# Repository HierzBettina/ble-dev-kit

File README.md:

*Note*: I have ceased working on projects with the HM-10 and the CC2541. The difficulties of dealing with the IAR toolchain are too great. I now recommend [ARM mbed solutions](https://developer.mbed.org/platforms/Nordic-nRF51822/) if you intend to pursue developing a BLE peripheral. I am leaving the resources I was able to gather online in case someone has use for them, but I cannot provide support.

BLE Dev Kit
====

Getting into low power Bluetooth peripheral prototyping can get expensive quickly. This project aims to chart out and the document the cheapest, easiest way to create a true, custom peripheral with its own profile. Head on over the [wiki](https://github.com/nickswalker/ble-dev-kit/wiki) to read more.

Hardware
----
A sub ten dollar CC2541 development board based on the HM-10 module. This board is a fork of Ladvien's excellent work with the module.
 
Firmware
----
On-board application and profile examples.

Software
----
Client application examples (iOS).

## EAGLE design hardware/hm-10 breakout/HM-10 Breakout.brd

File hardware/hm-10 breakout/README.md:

HM-10 Breakout Board
====================

This is a slight modification of [Ladvien's board](https://github.com/Ladvien/HM-10). This version has more accurate pin notations and removes routes to unused pins on the HM-10, thereby shrinking the overall footprint of the board. 
The HM-10's on board TI CC2541 is fully programmable with CC-Debugger or SmartRF04EB. See this repo's [wiki](https://github.com/nickswalker/HM-10-breakout-board/wiki) for more resources.

## Bill of Materials

If you are planning on ordering the PCB through OSHPark, keep in mind that you will receive three copies. You may want to go ahead and order three times as many components. Digi-Key numbers are provided as a courtesy; check eBay or any other preferred supplier for better pricing. As long as the component matches the packaging a specifications, it should be fine.

At a bare minimum, the PCB and the HM-10 module are required. If you want to use UART but only have the capability of providing 5v, you will want to populate the level conversion components. However, this is /grossly/ inefficient and defeats the purpose of using a low power connection technology. Bridge the solder jumper to bypass the regulator circuit. You may consider simply regulating off board for development, using a cheap level converter like [this one](http://www.ebay.com/itm/1PC-New-5V-3V-IIC-UART-Level-Converter-Module-Adapter-4-Way-For-Arduino-/251384699933?pt=LH_DefaultDomain_0&hash=item3a87b21c1d).

Part (Digi-Key #) | Quantity | Optional (Required For)
:---------------- | :-------:| :----------------------
[Breakout PCB](https://oshpark.com/shared_projects/A6hoH6Fi)  | 1 | No
[HM-10 Module](http://www.fasttech.com/products/0/10004051/1292002-ti-cc2540-bluetooth-40-ble-2540-transparent-serial) | 1 | No
[0805 20kΩ Resistor](http://www.digikey.com/product-detail/en/RMCF0805JT20K0/RMCF0805JT20K0CT-ND/1942580) (RMCF0805JT20K0CT-ND) | 1 | Yes (UART level conversion)
[0805 10kΩ Resistor](http://www.digikey.com/product-detail/en/RMCF0805FT10K0/RMCF0805FT10K0DKR-ND/1943341) (RMCF0805FT10K0CT-ND) | 3 | Yes (UART level conversion)
[0603 LED](http://www.digikey.com/product-detail/en/LTST-C191KRKT/160-1447-1-ND/386836) (160-1447-1-ND) | 1 | Yes (LEDs)
[0603 LED (>3v drop)](http://www.digikey.com/product-detail/en/APT1608QBC%2FD/754-1434-1-ND/2163792) (754-1434-1-ND) | 2 | Yes (LEDs)
[0805 470Ω Resistor](http://www.digikey.com/product-detail/en/RMCF0805JG470R/RMCF0805JG470RCT-ND/4425246) (RMCF0805JG470RCT-ND) | 3 | Yes (LEDs)
[SOT-23 MCP1700 Voltage Regulator](http://www.digikey.com/product-detail/en/MCP1700T-3302E%2FTT/MCP1700T3302ETTCT-ND/652677) (MCP1700T3302ETTCT-ND) | 1 | Yes (voltage regulator)
[0805 1uF Capacitor](http://www.digikey.com/product-detail/en/JMK105BJ105KV-F/587-1231-1-ND/931008) (587-1231-1-ND) | 1 | Yes (Voltage regulator)

The silkscreen doesn't include values, so be sure to have it open in front of you while you assemble.

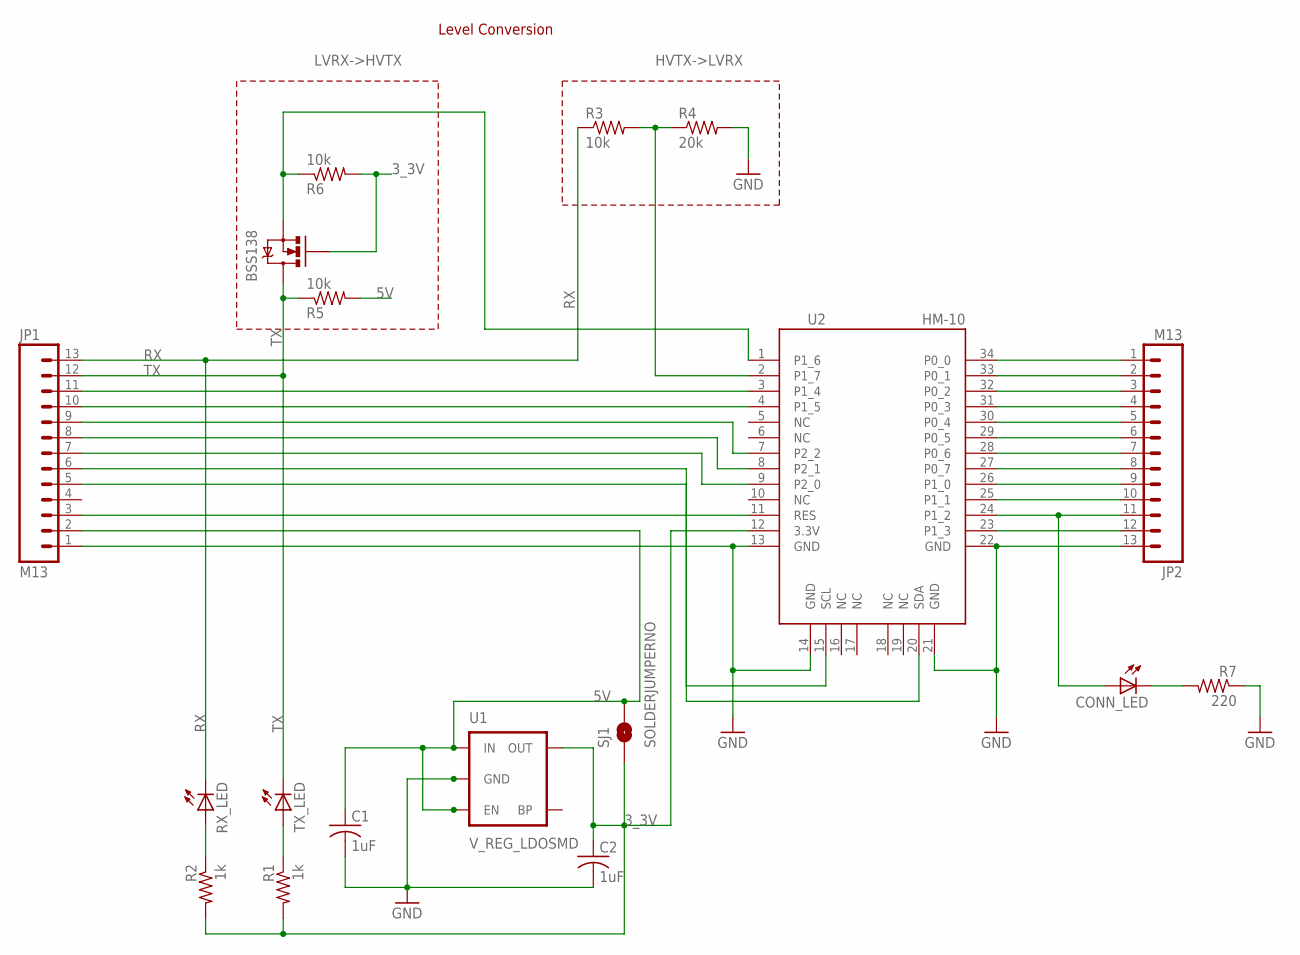
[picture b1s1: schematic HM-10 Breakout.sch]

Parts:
BSS138: MOSFET-NCHANNELSMD; SOT23-3
C1, C2: 1uF; C0805K
CONN_LED: LED0603; LED-0603
JP1, JP2: M13; 1X13
R1, R2: 1k; M0805
R3, R5, R6: 10k; M0805
R4: 20k; M0805
R7: 220; M0805
RX_LED: LED0603; LED-0603
SJ1: SOLDERJUMPERNO; SJ_2S-NO
TX_LED: LED0603; LED-0603
U1: V_REG_LDOSMD; SOT23-5
U2: HM-10

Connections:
3_3V: BSS138.1 (G), C2.1, R1.2, R2.2, R6.2, SJ1.1, U1.5 (OUT), U2.12 (3.3V)
5V: C1.1, JP1.2, R5.2, SJ1.2, U1.1 (IN), U1.3 (EN)
GND: C1.2, C2.2, JP1.1, JP2.13, R4.2, R7.1, U1.2 (GND), U2.13 (GND), U2.14 (GND), U2.21 (GND), U2.22 (GND)
HVTX->LVRX: R3.2, R4.1, U2.2 (P1_7)
LVRX->HVTX: BSS138.2 (S), R6.1, U2.1 (P1_6)
unnamed: CONN_LED.A, JP2.11, U2.24 (P1_2)
unnamed: JP1.3, U2.11 (RES)
unnamed: JP1.5, U2.15 (SCL)
unnamed: JP1.9, U2.7 (P2_2)
unnamed: JP1.8, U2.8 (P2_1)
unnamed: JP1.7, U2.9 (P2_0)
unnamed: JP2.10, U2.25 (P1_1)
unnamed: JP1.6, U2.20 (SDA)
unnamed: JP1.10, U2.4 (P1_5)
unnamed: JP1.11, U2.3 (P1_4)
unnamed: JP2.9, U2.26 (P1_0)
unnamed: JP2.8, U2.27 (P0_7)
unnamed: JP2.7, U2.28 (P0_6)
unnamed: JP2.6, U2.29 (P0_5)
unnamed: JP2.5, U2.30 (P0_4)
unnamed: JP2.4, U2.31 (P0_3)
unnamed: JP2.3, U2.32 (P0_2)
unnamed: JP2.2, U2.33 (P0_1)
unnamed: JP2.1, U2.34 (P0_0)
unnamed: JP2.12, U2.23 (P1_3)
unnamed: R1.1, TX_LED.A
unnamed: CONN_LED.C, R7.2
unnamed: R2.1, RX_LED.A
RX: JP1.13, R3.1, RX_LED.C
TX: BSS138.3 (D), JP1.12, R5.1, TX_LED.C

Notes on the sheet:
Level Conversion

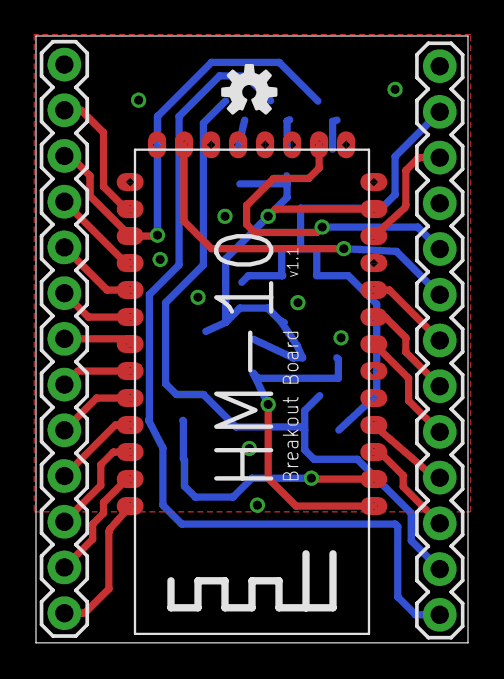
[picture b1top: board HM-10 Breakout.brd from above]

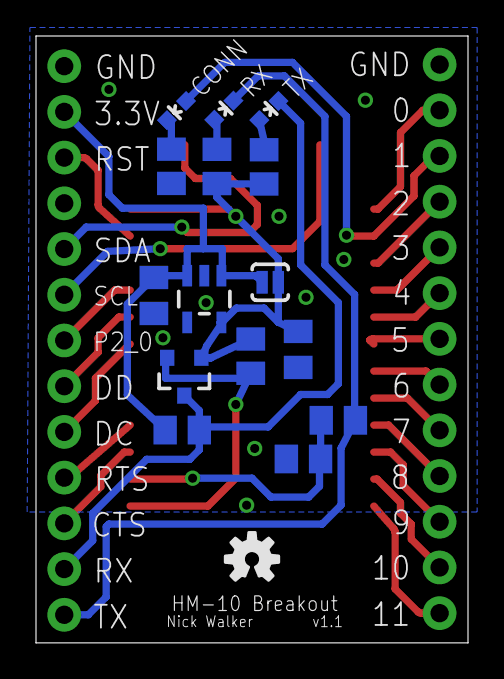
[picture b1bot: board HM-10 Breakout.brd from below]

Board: 2 copper layers, 24.0 x 33.7 mm, 20 parts (16 on the bottom side), 30 nets.

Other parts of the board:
U$1, U$2: OSHW-LOGO-S

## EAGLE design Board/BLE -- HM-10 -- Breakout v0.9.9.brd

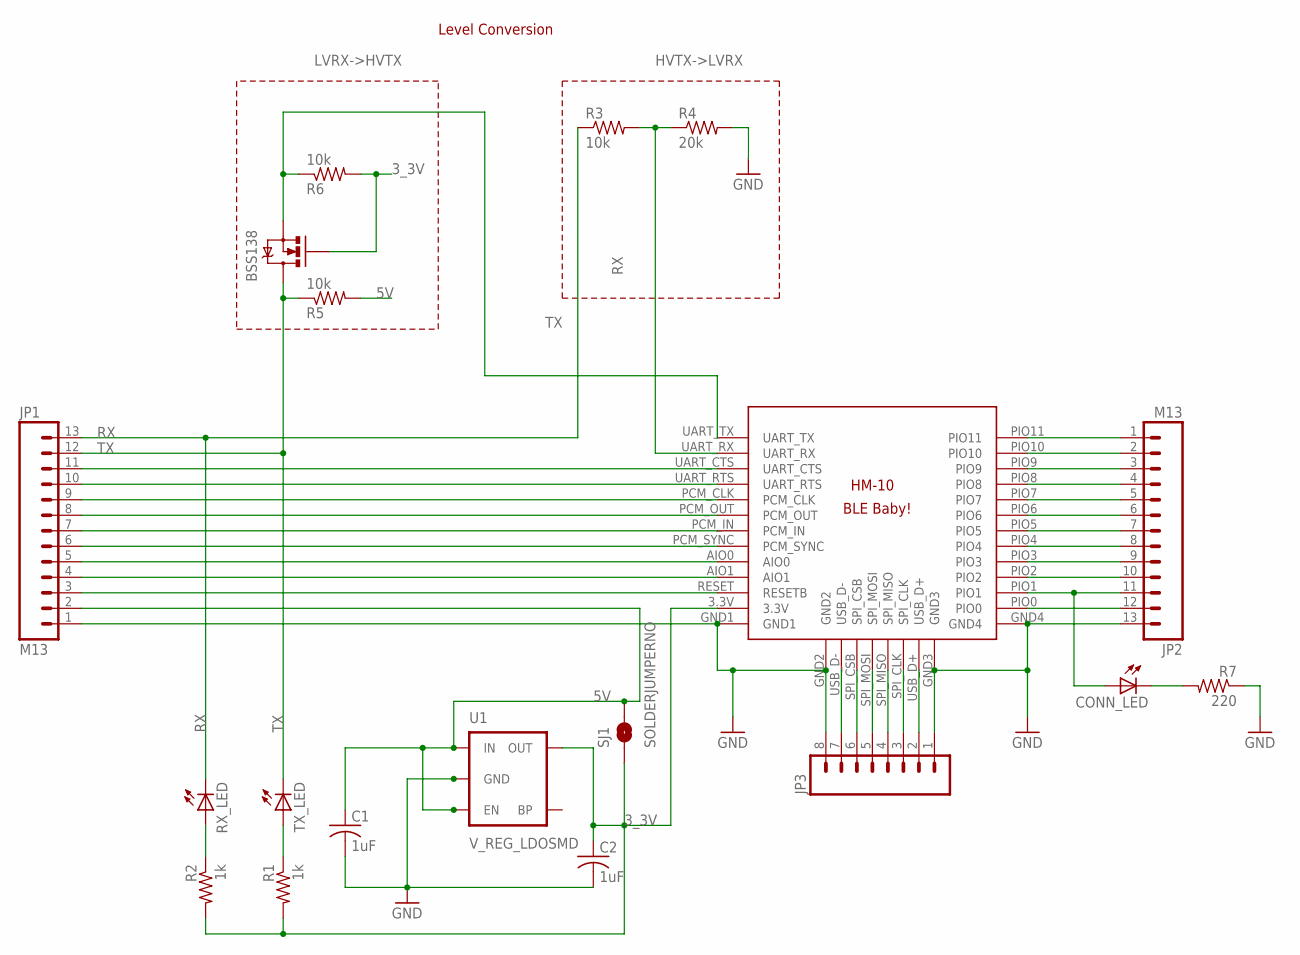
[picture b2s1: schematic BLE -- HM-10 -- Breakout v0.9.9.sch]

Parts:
BSS138: MOSFET-NCHANNELSMD; SOT23-3
C1, C2: 1uF; C0805K
CONN_LED: LED0603; LED-0603
JP1, JP2: M13; 1X13
JP3: M081X08; 1X08
R1, R2: 1k; M0805
R3, R5, R6: 10k; M0805
R4: 20k; M0805
R7: 220; M0805
RX_LED: LED0603; LED-0603
SJ1: SOLDERJUMPERNO; SJ_2S-NO
TX_LED: LED0603; LED-0603
U1: V_REG_LDOSMD; SOT23-5
U$1: BLE-HM-10

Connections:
3_3V: BSS138.1 (G), C2.1, R1.2, R2.2, R6.2, SJ1.1, U1.5 (OUT), U$1.3.3V
5V: C1.1, JP1.2, R5.2, SJ1.2, U1.1 (IN), U1.3 (EN)
GND: C1.2, C2.2, JP1.1, JP2.13, JP3.1, JP3.8, R4.2, R7.1, U1.2 (GND), U$1.GND1, U$1.GND2, U$1.GND3, U$1.GND4
HVTX->LVRX: R3.2, R4.1, U$1.UART_RX
LVRX->HVTX: BSS138.2 (S), R6.1, U$1.UART_TX
unnamed: CONN_LED.A, JP2.11, U$1.PIO1
unnamed: JP1.3, U$1.RESET (RESETB)
unnamed: JP1.4, U$1.AIO1
unnamed: JP1.5, U$1.AIO0
unnamed: JP1.6, U$1.PCM_SYNC
unnamed: JP1.7, U$1.PCM_IN
unnamed: JP1.8, U$1.PCM_OUT
unnamed: JP1.9, U$1.PCM_CLK
unnamed: JP1.10, U$1.UART_RTS
unnamed: JP1.11, U$1.UART_CTS
unnamed: JP2.1, U$1.PIO11
unnamed: JP2.2, U$1.PIO10
unnamed: JP2.3, U$1.PIO9
unnamed: JP2.4, U$1.PIO8
unnamed: JP2.5, U$1.PIO7
unnamed: JP2.6, U$1.PIO6
unnamed: JP2.7, U$1.PIO5
unnamed: JP2.8, U$1.PIO4
unnamed: JP2.9, U$1.PIO3
unnamed: JP2.10, U$1.PIO2
unnamed: R1.1, TX_LED.A
unnamed: JP2.12, U$1.PIO0
unnamed: CONN_LED.C, R7.2
unnamed: R2.1, RX_LED.A
unnamed: JP3.2, U$1.USB_D+
unnamed: JP3.3, U$1.SPI_CLK
unnamed: JP3.4, U$1.SPI_MISO
unnamed: JP3.5, U$1.SPI_MOSI
unnamed: JP3.6, U$1.SPI_CSB
unnamed: JP3.7, U$1.USB_D-
RX: JP1.13, R3.1, RX_LED.C
TX: BSS138.3 (D), JP1.12, R5.1, TX_LED.C

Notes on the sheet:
Level Conversion

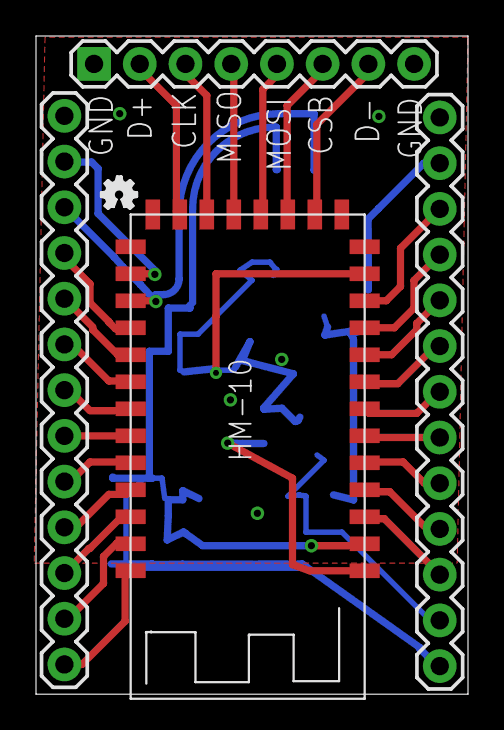
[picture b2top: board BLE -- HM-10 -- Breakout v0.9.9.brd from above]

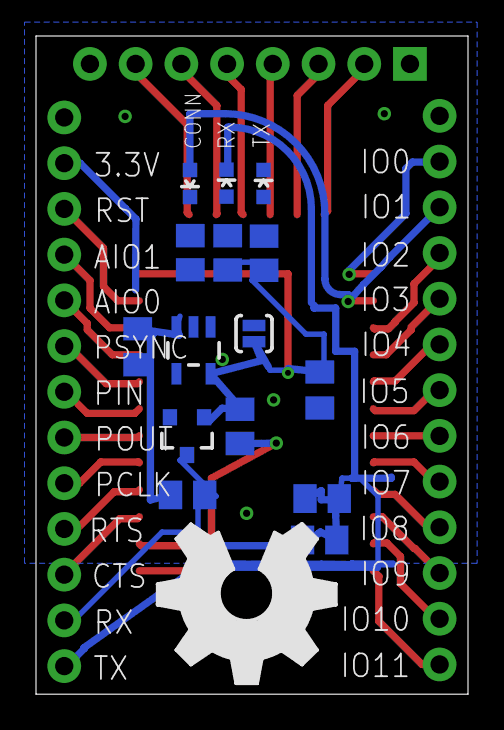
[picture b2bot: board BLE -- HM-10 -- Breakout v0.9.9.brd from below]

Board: 2 copper layers, 24.0 x 36.6 mm, 21 parts (16 on the bottom side), 37 nets.

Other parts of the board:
U$2: OSHW_FILLX350_NOTEXT
U$3: OSHW_FILLX70_NOTEXT

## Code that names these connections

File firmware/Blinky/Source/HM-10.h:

#ifndef HM_10
#define HM_10

#define PIN0 P1_3
#define PIN1 P1_2
#define PIN2 P1_1
#define PIN3 P1_0

#define PIN4 P0_7
#define PIN5 P0_6
#define PIN6 P0_5
#define PIN7 P0_4
#define PIN8 P0_3
#define PIN9 P0_2
#define PIN10 P0_1
#define PIN11 P0_0

#endif /* HM-10 */

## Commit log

2014-04-22 Update readme
    Update BoM
    Add images of board
    New links
2014-04-22 Remove variants
    Start updating board
    Normalize PCB typography
2014-04-22 Update README.md
    Fix image positioning
    Add datasheet link
2014-04-22 Update README.md
    Organize links
2014-04-26 Overhaul PCB
    Cleanup typography on silkscreen
    Remove no connection lines
    Replace HM-10 Eagle part with a more faithful version
2014-04-26 Update documentation
    Include photos of hm-10 front and back
    Updated readme to reflect changes to the board
2014-04-26 Update Docs
2014-04-26 Update README.md
    Update image spacing
2014-04-28 Update README.md
    Update link descriptions
    Link to OSHPark shared project
2014-04-29 Update README.md
    Remove reference to CC Debug header
2014-04-29 Update README.md
    Add part number for capacitor
2014-04-30 Update README.md
    Add Biscuit
2014-05-01 Update README.md
    Clean up link formatting
    Switch part references to CC2451 as per recent change in HM10 modules
2014-05-01 Update README.md
    Fix bad link
2014-05-04 Shrink board
    Remove top row of pins
    Change silkscreen to note change to SPI over USB
    Add version number and text to silkscreen
2014-05-10 Update README.md
    Add Radius Networks to links
2014-05-18 Update README.md
    Add BlueShield
2014-05-18 Shift components toward center on bottom layer
    Make pin description text larger
    Switch from DBGD to DD notation
    Rotate LED labels 45 degrees
2014-05-25 Tented vias
    Cleaned up routes more
2014-05-25 Update images
    Rotate LEDs 45 degrees
2014-06-01 Add OSHW logos back
    Add attribution text to bottom layer
2014-06-01 Update images
2014-06-01 Update README.md
    Update to latest OSHPark link
2014-06-01 Update README.md
    Add note about the solder jumper
2014-06-01 Update README.md
    Add note about why the regulator is not preferable.
2014-08-08 Update README.md
    Remove the growing links section and link to the wiki instead
2014-08-09 Fix swapped debug signals
    Update images
    Update eagle files to v7
2014-08-13 Pivot the project
    Start moving the project toward a more inclusive goal
    Add a blinky firmware example
2014-08-13 Clean up readme
2014-08-13 Move hm-10 breakout to own directory
    Room to accommodate future boards (HM-11)
2014-08-13 Strip down Blinky more
    Remove all but one characteristic
    Finish renaming files
    Add macros for declaring GATT attribute tables
    Remove custom devinfoservice
2014-08-13 Make Blinky iOS controllable
    Remove build directories from git
    Fix an issue with the attribute macros related to UUID length
    Add HM-10 pin defines
    Add proper custom dev info service
2014-10-11 Fix grammar in readme
2014-10-20 Fix broken image links
2014-10-20 Add RSSI Probe client example
    Tweak readmes
2014-10-20 Improve logging
    Add a log event counter to make taking samples easier
    Split scanning feature to use its own log
    Improve CSV formating
2014-12-29 Refactor buffering code
    Create average buffer class to simplify meters
    Add basic tests for metering data structure
    Untrack xcode cruft
2015-01-02 Run classes through code styler
2015-01-11 Add missing .ewp that was preventing compilation
2015-05-19 Add a note about ceasing development
2015-05-19 Add "no support" notice

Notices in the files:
parts and their libraries:
SparkFun: Licensing: CC v3.0 Share-Alike You are welcome to use this library for commercial purposes.
SparkFun-Aesthetics: Licensing: Creative Commons ShareAlike 4.0 International - https://creativecommons.org/licenses/by-sa/4.0
